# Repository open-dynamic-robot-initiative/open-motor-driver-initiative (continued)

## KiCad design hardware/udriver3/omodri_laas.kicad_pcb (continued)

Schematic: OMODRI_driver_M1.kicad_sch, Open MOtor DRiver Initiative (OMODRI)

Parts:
C74, C77: 1uF; C_0402_1005Metric; Rated Voltage 35V; Part No C1005X5R1V105K050BE; DigiKey 445-175218-1-ND
C75: 10uF; C_1210_3225Metric; Rated Voltage 75V; Part No C3225X7R1N106K250AC; Farnell 3416259
C76: 100nF; C_0603_1608Metric; Rated Voltage 100V; Part No GRM188R72A104KA35D; Farnell 1828921
C78: 1uF; C_0201_0603Metric; Rated Voltage 10V; Part No GRM033C81A105ME05D; DigiKey 490-13219-1-ND
C79: 47nF; C_0603_1608Metric; Rated Voltage 100V; Part No C1608X7S2A473K080AB; DigiKey 445-6032-1-ND
C80, C86, C87: 1.8nF; C_0201_0603Metric; Rated Voltage 50V; Part No GRM033R71E182KA12D; DigiKey 490-GRM033R71E182KA12DTR-ND
C81, C88, C89: 470nF; C_0201_0603Metric; Rated Voltage 25V; Part No GRM033R60J474ME90D; DigiKey 490-10410-1-ND
C82: 100nF; C_0201_0603Metric; Rated Voltage 10V; Part No GRM033R61E104KE14J; Farnell 3790414
C83, C84, C85: 1.8nF; C_0201_0603Metric; Rated Voltage 25V; Part No GRM033R71E182KA12D; DigiKey 490-GRM033R71E182KA12DTR-ND
D3: LED RED; LED_0402_1005Metric; Part No HSMC-C280; DigiKey 516-3060-1-ND
J11: Conn_01x03; AMASS_MR30PW-FB_1x03_P3.50mm_Horizontal
Q1, Q2, Q3: CSD88599Q5DC; VSON_CLIP_22; Part No CSD88599Q5DC; DigiKey 296-48289-1-ND
R7, R47: 10k; R_0201_0603Metric; Part No ERJ-1GNF1002C; DigiKey P122414CT-ND
R34, R38, R39: 100k; R_0402_1005Metric; Rated Voltage 50; Part No ERJ-2RKF1003X; DigiKey P100KLCT-ND
R35, R42, R44: 0.005; FC4L64; Part No FC4L64R005FER; DigiKey FC4L64R005FERCT-ND
R36, R43, R45: 5.1k; R_0402_1005Metric; Rated Voltage 50; Part No ERJ-2RKF5101X; DigiKey P5.10KLCT-ND
R37, R40, R41: 120; R_0201_0603Metric; Part No ERJ-1GNF1200C; DigiKey P122692CT-ND
R46: 470; R_0201_0603Metric; Part No ERJ-1GNF4701C; DigiKey P123031CT-ND
U19: DRV8353S; QFN-40-1EP_6x6mm_P0.5mm_EP4.6x4.6mm; Part No DRV8353SRTAT; DigiKey 296-DRV8353SRTATCT-ND

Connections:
/OMODRI_GPIO/DRV1_GPIO_EN: U19.31 (ENABLE); also elsewhere on the board
/OMODRI_GPIO/DRV_SPI_CLK: U19.29 (SCLK); also elsewhere on the board
/OMODRI_GPIO/DRV_SPI_SIMO: U19.28 (SDI); also elsewhere on the board
/OMODRI_GPIO/DRV_SPI_SOMI: R7.1, U19.27 (SDO); also elsewhere on the board
/OMODRI_GPIO/M1_Ia: C85.1, R41.1; also elsewhere on the board
/OMODRI_GPIO/M1_Ib: C84.1, R40.1; also elsewhere on the board
/OMODRI_GPIO/M1_Ic: C83.1, R37.1; also elsewhere on the board
/OMODRI_GPIO/M1_Va: C81.1, R34.2, R36.1; also elsewhere on the board
/OMODRI_GPIO/M1_Vb: C88.1, R38.2, R43.1; also elsewhere on the board
/OMODRI_GPIO/M1_Vc: C89.1, R39.2, R45.1; also elsewhere on the board
/OMODRI_GPIO/~DRV1_GPIO_CSn~: U19.30 (~SCS); also elsewhere on the board
/OMODRI_GPIO/~DRV1_GPIO_FAULTn~: R46.1, R47.1, U19.26 (~FAULT); also elsewhere on the board
/OMODRI_driver_M1/CPH: C79.1, U19.2 (CPH)
/OMODRI_driver_M1/CPL: C79.2, U19.1 (CPL)
/OMODRI_driver_M1/DVDD: C78.1, U19.38 (DVDD)
/OMODRI_driver_M1/GHA: Q1.1 (GH), U19.6 (GHA)
/OMODRI_driver_M1/GHB: Q2.1 (GH), U19.15 (GHB)
/OMODRI_driver_M1/GHC: Q3.1 (GH), U19.16 (GHC)
/OMODRI_driver_M1/GLA: Q1.22 (GL), U19.8 (GLA)
/OMODRI_driver_M1/GLB: Q2.22 (GL), U19.13 (GLB)
/OMODRI_driver_M1/GLC: Q3.22 (GL), U19.18 (GLC)
/OMODRI_driver_M1/INHA: U19.32 (INHA); also elsewhere on the board
/OMODRI_driver_M1/INHB: U19.34 (INHB); also elsewhere on the board
/OMODRI_driver_M1/INHC: U19.36 (INHC); also elsewhere on the board
/OMODRI_driver_M1/INLA: U19.33 (INLA); also elsewhere on the board
/OMODRI_driver_M1/INLB: U19.35 (INLB); also elsewhere on the board
/OMODRI_driver_M1/INLC: U19.37 (INLC); also elsewhere on the board
/OMODRI_driver_M1/MOTOR_CH1: J11.1, Q1.3 (VSW), Q1.4 (VSW), Q1.5 (VSW), Q1.6 (VSW), Q1.7 (VSW), Q1.8 (VSW), Q1.9 (VSW), Q1.10 (VSW), Q1.11 (VSW), R34.1
/OMODRI_driver_M1/MOTOR_CH2: J11.2, Q2.3 (VSW), Q2.4 (VSW), Q2.5 (VSW), Q2.6 (VSW), Q2.7 (VSW), Q2.8 (VSW), Q2.9 (VSW), Q2.10 (VSW), Q2.11 (VSW), R38.1
/OMODRI_driver_M1/MOTOR_CH3: J11.3, Q3.3 (VSW), Q3.4 (VSW), Q3.5 (VSW), Q3.6 (VSW), Q3.7 (VSW), Q3.8 (VSW), Q3.9 (VSW), Q3.10 (VSW), Q3.11 (VSW), R39.1
/OMODRI_driver_M1/OUT_M1_CH1: Q1.12 (PGND), Q1.13 (PGND), Q1.14 (PGND), Q1.15 (PGND), Q1.16 (PGND), Q1.17 (PGND), Q1.18 (PGND), Q1.19 (PGND), Q1.20 (PGND), R35.1
/OMODRI_driver_M1/OUT_M1_CH2: Q2.12 (PGND), Q2.13 (PGND), Q2.14 (PGND), Q2.15 (PGND), Q2.16 (PGND), Q2.17 (PGND), Q2.18 (PGND), Q2.19 (PGND), Q2.20 (PGND), R42.4
/OMODRI_driver_M1/OUT_M1_CH3: Q3.12 (PGND), Q3.13 (PGND), Q3.14 (PGND), Q3.15 (PGND), Q3.16 (PGND), Q3.17 (PGND), Q3.18 (PGND), Q3.19 (PGND), Q3.20 (PGND), R44.4
/OMODRI_driver_M1/SHA: Q1.2 (SH), U19.7 (SHA)
/OMODRI_driver_M1/SHB: Q2.2 (SH), U19.14 (SHB)
/OMODRI_driver_M1/SHC: Q3.2 (SH), U19.17 (SHC)
/OMODRI_driver_M1/SNA: C80.2, R35.3, U19.10 (SNA)
/OMODRI_driver_M1/SNB: C86.2, R42.2, U19.11 (SNB)
/OMODRI_driver_M1/SNC: C87.2, R44.2, U19.20 (SNC)
/OMODRI_driver_M1/SPA: C80.1, R35.2, U19.9 (SPA)
/OMODRI_driver_M1/SPB: C86.1, R42.3, U19.12 (SPB)
/OMODRI_driver_M1/SPC: C87.1, R44.3, U19.19 (SPC)
/OMODRI_driver_M1/VCP_DRV: C74.2, U19.5 (VCP)
/OMODRI_driver_M1/VGLS: C77.2, U19.40 (VGLS)
unnamed: D3.1 (K), R46.2
unnamed: R37.2, U19.21 (SOC)
unnamed: R40.2, U19.22 (SOB)
unnamed: R41.2, U19.23 (SOA)
REF_3V0_BUF: C82.1, U19.24 (VREF); also elsewhere on the board
VDD_3V3: D3.2 (A), R7.2, R47.2; also elsewhere on the board

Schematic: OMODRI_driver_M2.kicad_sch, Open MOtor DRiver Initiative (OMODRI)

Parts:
C90, C93: 1uF; C_0402_1005Metric; Rated Voltage 35V; Part No C1005X5R1V105K050BE; DigiKey 445-175218-1-ND
C91: 10uF; C_1210_3225Metric; Rated Voltage 75V; Part No C3225X7R1N106K250AC; Farnell 3416259
C92: 100nF; C_0603_1608Metric; Rated Voltage 100V; Part No GRM188R72A104KA35D; Farnell 1828921
C94: 1uF; C_0201_0603Metric; Rated Voltage 10V; Part No GRM033C81A105ME05D; DigiKey 490-13219-1-ND
C95: 47nF; C_0603_1608Metric; Rated Voltage 100V; Part No C1608X7S2A473K080AB; DigiKey 445-6032-1-ND
C96, C102, C103: 1.8nF; C_0201_0603Metric; Rated Voltage 50V; Part No GRM033R71E182KA12D; DigiKey 490-GRM033R71E182KA12DTR-ND
C97, C104, C105: 470nF; C_0201_0603Metric; Rated Voltage 25V; Part No GRM033R60J474ME90D; DigiKey 490-10410-1-ND
C98: 100nF; C_0201_0603Metric; Rated Voltage 10V; Part No GRM033R61E104KE14J; Farnell 3790414
C99, C100, C101: 1.8nF; C_0201_0603Metric; Rated Voltage 25V; Part No GRM033R71E182KA12D; DigiKey 490-GRM033R71E182KA12DTR-ND
D4: LED RED; LED_0402_1005Metric; Part No HSMC-C280; DigiKey 516-3060-1-ND
J12: Conn_01x03; AMASS_MR30PW-FB_1x03_P3.50mm_Horizontal
Q4, Q5, Q6: CSD88599Q5DC; VSON_CLIP_22; Part No CSD88599Q5DC; DigiKey 296-48289-1-ND
R48, R52, R53: 100k; R_0402_1005Metric; Rated Voltage 50; Part No ERJ-2RKF1003X; DigiKey P100KLCT-ND
R49, R56, R58: 0.005; FC4L64; Part No FC4L64R005FER; DigiKey FC4L64R005FERCT-ND
R50, R57, R59: 5.1k; R_0402_1005Metric; Rated Voltage 50; Part No ERJ-2RKF5101X; DigiKey P5.10KLCT-ND
R51, R54, R55: 120; R_0201_0603Metric; Part No ERJ-1GNF1200C; DigiKey P122692CT-ND
R60: 470; R_0201_0603Metric; Part No ERJ-1GNF4701C; DigiKey P123031CT-ND
R61: 10k; R_0201_0603Metric; Part No ERJ-1GNF1002C; DigiKey P122414CT-ND
U20: DRV8353S; QFN-40-1EP_6x6mm_P0.5mm_EP4.6x4.6mm; Part No DRV8353SRTAT; DigiKey 296-DRV8353SRTATCT-ND

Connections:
/OMODRI_GPIO/DRV2_GPIO_EN: U20.31 (ENABLE); also elsewhere on the board
/OMODRI_GPIO/DRV_SPI_CLK: U20.29 (SCLK); also elsewhere on the board
/OMODRI_GPIO/DRV_SPI_SIMO: U20.28 (SDI); also elsewhere on the board
/OMODRI_GPIO/DRV_SPI_SOMI: U20.27 (SDO); also elsewhere on the board
/OMODRI_GPIO/M2_Ia: C101.1, R55.1; also elsewhere on the board
/OMODRI_GPIO/M2_Ib: C100.1, R54.1; also elsewhere on the board
/OMODRI_GPIO/M2_Ic: C99.1, R51.1; also elsewhere on the board
/OMODRI_GPIO/M2_Va: C97.1, R48.2, R50.1; also elsewhere on the board
/OMODRI_GPIO/M2_Vb: C104.1, R52.2, R57.1; also elsewhere on the board
/OMODRI_GPIO/M2_Vc: C105.1, R53.2, R59.1; also elsewhere on the board
/OMODRI_GPIO/~DRV2_GPIO_CSn~: U20.30 (~SCS); also elsewhere on the board
/OMODRI_GPIO/~DRV2_GPIO_FAULTn~: R60.1, R61.1, U20.26 (~FAULT); also elsewhere on the board
/OMODRI_driver_M2/CPH: C95.1, U20.2 (CPH)
/OMODRI_driver_M2/CPL: C95.2, U20.1 (CPL)
/OMODRI_driver_M2/DVDD: C94.1, U20.38 (DVDD)
/OMODRI_driver_M2/GHA: Q4.1 (GH), U20.6 (GHA)
/OMODRI_driver_M2/GHB: Q5.1 (GH), U20.15 (GHB)
/OMODRI_driver_M2/GHC: Q6.1 (GH), U20.16 (GHC)
/OMODRI_driver_M2/GLA: Q4.22 (GL), U20.8 (GLA)
/OMODRI_driver_M2/GLB: Q5.22 (GL), U20.13 (GLB)
/OMODRI_driver_M2/GLC: Q6.22 (GL), U20.18 (GLC)
/OMODRI_driver_M2/INHA: U20.32 (INHA); also elsewhere on the board
/OMODRI_driver_M2/INHB: U20.34 (INHB); also elsewhere on the board
/OMODRI_driver_M2/INHC: U20.36 (INHC); also elsewhere on the board
/OMODRI_driver_M2/INLA: U20.33 (INLA); also elsewhere on the board
/OMODRI_driver_M2/INLB: U20.35 (INLB); also elsewhere on the board
/OMODRI_driver_M2/INLC: U20.37 (INLC); also elsewhere on the board
/OMODRI_driver_M2/MOTOR_CH1: J12.1, Q4.3 (VSW), Q4.4 (VSW), Q4.5 (VSW), Q4.6 (VSW), Q4.7 (VSW), Q4.8 (VSW), Q4.9 (VSW), Q4.10 (VSW), Q4.11 (VSW), R48.1
/OMODRI_driver_M2/MOTOR_CH2: J12.2, Q5.3 (VSW), Q5.4 (VSW), Q5.5 (VSW), Q5.6 (VSW), Q5.7 (VSW), Q5.8 (VSW), Q5.9 (VSW), Q5.10 (VSW), Q5.11 (VSW), R52.1
/OMODRI_driver_M2/MOTOR_CH3: J12.3, Q6.3 (VSW), Q6.4 (VSW), Q6.5 (VSW), Q6.6 (VSW), Q6.7 (VSW), Q6.8 (VSW), Q6.9 (VSW), Q6.10 (VSW), Q6.11 (VSW), R53.1
/OMODRI_driver_M2/OUT_M2_CH1: Q4.12 (PGND), Q4.13 (PGND), Q4.14 (PGND), Q4.15 (PGND), Q4.16 (PGND), Q4.17 (PGND), Q4.18 (PGND), Q4.19 (PGND), Q4.20 (PGND), R49.1
/OMODRI_driver_M2/OUT_M2_CH2: Q5.12 (PGND), Q5.13 (PGND), Q5.14 (PGND), Q5.15 (PGND), Q5.16 (PGND), Q5.17 (PGND), Q5.18 (PGND), Q5.19 (PGND), Q5.20 (PGND), R56.1
/OMODRI_driver_M2/OUT_M2_CH3: Q6.12 (PGND), Q6.13 (PGND), Q6.14 (PGND), Q6.15 (PGND), Q6.16 (PGND), Q6.17 (PGND), Q6.18 (PGND), Q6.19 (PGND), Q6.20 (PGND), R58.4
/OMODRI_driver_M2/SHA: Q4.2 (SH), U20.7 (SHA)
/OMODRI_driver_M2/SHB: Q5.2 (SH), U20.14 (SHB)
/OMODRI_driver_M2/SHC: Q6.2 (SH), U20.17 (SHC)
/OMODRI_driver_M2/SNA: C96.2, R49.3, U20.10 (SNA)
/OMODRI_driver_M2/SNB: C102.2, R56.3, U20.11 (SNB)
/OMODRI_driver_M2/SNC: C103.2, R58.2, U20.20 (SNC)
/OMODRI_driver_M2/SPA: C96.1, R49.2, U20.9 (SPA)
/OMODRI_driver_M2/SPB: C102.1, R56.2, U20.12 (SPB)
/OMODRI_driver_M2/SPC: C103.1, R58.3, U20.19 (SPC)
/OMODRI_driver_M2/VCP_DRV: C90.2, U20.5 (VCP)
/OMODRI_driver_M2/VGLS: C93.2, U20.40 (VGLS)
unnamed: D4.1 (K), R60.2
unnamed: R51.2, U20.21 (SOC)
unnamed: R54.2, U20.22 (SOB)
unnamed: R55.2, U20.23 (SOA)
REF_3V0_BUF: C98.1, U20.24 (VREF); also elsewhere on the board
VDD_3V3: D4.2 (A), R61.2; also elsewhere on the board

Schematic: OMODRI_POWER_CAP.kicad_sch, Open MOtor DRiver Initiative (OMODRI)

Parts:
C11, C114, C115, C116: 22uF; C_2220_5650Metric; Rated Voltage 100V; Part No C5750X7S2A226M280KB; DigiKey 445-C5750X7S2A226M280KBCT-ND
C112: 10nF; C_0201_0603Metric; Rated Voltage 25V; Part No GRM033R71E103KE14D; DigiKey 490-14454-1-ND
D11: TPD1E04U04; D_0201_0603Metric; Part No TPD1E04U04DPLT; DigiKey 296-47862-1-ND
J13: Conn_01x02; AMASS_XT30PW-M_1x02_P2.50mm_Horizontal
R62: 100k; R_0402_1005Metric; Rated Voltage 50; Part No ERJ-2RKF1003X; DigiKey P100KLCT-ND
R63: 5.1k; R_0402_1005Metric; Rated Voltage 50; Part No ERJ-2RKF5101X; DigiKey P5.10KLCT-ND

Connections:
/OMODRI_GPIO/M1_Vbus: C112.1, D11.1 (IO), R62.2, R63.1; also elsewhere on the board

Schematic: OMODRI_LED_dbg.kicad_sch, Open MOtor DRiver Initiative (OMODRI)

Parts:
D5: WS2812B; LED_WS2812B_PLCC4_5.0x5.0mm_P3.2mm; Part No WS2812B 5050; DigiKey 1568-COM-16347CT-ND

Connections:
/OMODRI_GPIO/WS2812B_CMD: D5.4 (DIN); also elsewhere on the board
VDD_3V3: D5.1 (VDD); also elsewhere on the board

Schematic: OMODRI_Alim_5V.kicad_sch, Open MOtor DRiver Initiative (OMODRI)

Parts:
C9: 10uF; C_1210_3225Metric; Rated Voltage 75V; Part No C3225X7R1N106K250AC; Farnell 3416259
C10, C30: 100nF; C_0603_1608Metric; Rated Voltage 100V; Part No GRM188R72A104KA35D; Farnell 1828921
C12: 1uF; C_0201_0603Metric; Rated Voltage 10V; Part No GRM033C81A105ME05D; DigiKey 490-13219-1-ND
C13: 10uF; C_0603_1608Metric; Rated Voltage 10V; Part No GRM188R61A106ME69D; DigiKey 490-10475-1-ND
L1: 22uH; L_Wuerth_MAPI-4020; Part No MPL-SE4030-220
R3, R69: 100k; R_0201_0603Metric; Part No ERJ-1GNF1003C; DigiKey P122655CT-ND
R68, R70, R71, R72: 76.8k; R_0201_0603Metric
U2: MP4572GQB

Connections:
unnamed: R70.1, R71.2, R72.1

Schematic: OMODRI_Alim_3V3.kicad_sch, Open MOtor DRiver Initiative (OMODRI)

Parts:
C14, C16, C19: 10uF; C_0603_1608Metric; Rated Voltage 10V; Part No GRM188R61A106ME69D; DigiKey 490-10475-1-ND
C15, C17: 1uF; C_0201_0603Metric; Rated Voltage 10V; Part No GRM033C81A105ME05D; DigiKey 490-13219-1-ND
FB1, FB2: 220R@100MHz; L_0603_1608Metric; Part No BLM18SG221TN1D; DigiKey 490-5225-1-ND
R5: 100k; R_0201_0603Metric; Part No ERJ-1GNF1003C; DigiKey P122655CT-ND
R6: 22.1k; R_0201_0603Metric; Part No ERJ-1GNF2212C; DigiKey P122837CT-ND
U3: MPM3804GG; QFN-10_2x2mm_P0.5mm; Part No MPM3804GG; DigiKey 1589-1982-1-ND

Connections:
/Power distribution/OMODRI_Alim_3V3/3V3: C19.1, FB1.2, FB2.2, R5.1, U3.6 (VOUT), U3.7 (VOUT), U3.8 (VOUT)
/Power distribution/OMODRI_Alim_3V3/FB_3V3: R5.2, R6.1, U3.9 (FB)
/Power distribution/OMODRI_Alim_3V3/SW: U3.2 (SW), U3.3 (SW), U3.4 (SW)
VDDA_3V3: C16.1, C17.1, FB2.1; also elsewhere on the board
VDD_3V3: C14.1, C15.1, FB1.1; also elsewhere on the board

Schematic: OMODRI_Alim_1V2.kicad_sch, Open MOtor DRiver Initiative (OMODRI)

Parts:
C21, C22: 10uF; C_0603_1608Metric; Rated Voltage 10V; Part No GRM188R61A106ME69D; DigiKey 490-10475-1-ND
C23: 1uF; C_0201_0603Metric; Rated Voltage 10V; Part No GRM033C81A105ME05D; DigiKey 490-13219-1-ND
FB3: 220R@100MHz; L_0603_1608Metric; Part No BLM18SG221TN1D; DigiKey 490-5225-1-ND
R8, R9: 100k; R_0201_0603Metric; Part No ERJ-1GNF1003C; DigiKey P122655CT-ND
U4: MPM3804GG; QFN-10_2x2mm_P0.5mm; Part No MPM3804GG; DigiKey 1589-1982-1-ND

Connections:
/Power distribution/OMODRI_Alim_1V2/1V2: C21.1, FB3.2, R8.1, U4.6 (VOUT), U4.7 (VOUT), U4.8 (VOUT)
/Power distribution/OMODRI_Alim_1V2/FB_1V2: R8.2, R9.1, U4.9 (FB)
/Power distribution/OMODRI_Alim_1V2/SW: U4.2 (SW), U4.3 (SW), U4.4 (SW)
VDD_1V2: C22.1, C23.1, FB3.1; also elsewhere on the board

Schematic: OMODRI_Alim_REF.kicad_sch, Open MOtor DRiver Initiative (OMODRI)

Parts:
C26: 100nF; C_0201_0603Metric; Rated Voltage 10V; Part No GRM033R61E104KE14J; DigiKey 490-14571-1-ND
C27, C29: 1uF; C_0201_0603Metric; Rated Voltage 10V; Part No GRM033C81A105ME05D; DigiKey 490-13219-1-ND
C28: 10uF; C_0603_1608Metric; Rated Voltage 10V; Part No GRM188R61A106ME69D; DigiKey 490-10475-1-ND
U5: LT6654AIS6-3; TSOT-23-6; Part No LT6654AIS6-3#TRMPBF; DigiKey LT6654AIS6-3#TRMPBFCT-ND

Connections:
REF_3V0_BUF: C28.1, C29.1, U5.6 (VOUT); also elsewhere on the board
VDDA_3V3: C26.1, C27.1, U5.4 (VIN); also elsewhere on the board

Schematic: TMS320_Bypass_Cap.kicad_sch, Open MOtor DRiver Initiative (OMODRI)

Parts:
C34, C35, C36, C37, C38, C39, C40, C41, C42, C43, C44, C45, C46, C47, C48, C49, C50, C51, C52, C53, C54, C55, C56: 100nF; C_0201_0603Metric; Rated Voltage 10V; Part No GRM033R61E104KE14J; Farnell 3790414
R10, R13: 120; R_0201_0603Metric; Part No ERJ-1GNF1200C; DigiKey P122692CT-ND

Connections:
VDD_1V2: C34.1, C35.1, C36.1, C37.1, C38.1, C39.1, C40.1, R10.1, R13.1; also elsewhere on the board
VDD_3V3: C41.1, C42.1, C43.1, C44.1, C45.1, C46.1, C47.1, C48.1, C49.1, C50.1, C51.1, C52.1, C53.1, C54.1, C55.1, C56.1; also elsewhere on the board

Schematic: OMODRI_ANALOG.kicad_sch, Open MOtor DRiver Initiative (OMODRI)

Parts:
D2, D6, D7, D8, D9, D10, D12, D13: TPD1E04U04; D_0201_0603Metric; Part No TPD1E04U04DPLT; DigiKey 296-47862-1-ND
U1: TMS320F28388D; NFBGA_337; Part No F28388DZWTS; DigiKey 296-F28388DZWTS-ND

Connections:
/OMODRI_GPIO/ANALOG_IN1: D12.1 (IO), U1.T4 (ADCIN14); also elsewhere on the board
/OMODRI_GPIO/ANALOG_IN2: D13.1 (IO), U1.U4 (ADCIN15); also elsewhere on the board
/OMODRI_GPIO/M1_Ia: U1.U1 (ADCINA0); also elsewhere on the board
/OMODRI_GPIO/M1_Ib: U1.V2 (ADCINB0); also elsewhere on the board
/OMODRI_GPIO/M1_Ic: U1.T5 (ADCIND0); also elsewhere on the board
/OMODRI_GPIO/M1_Va: D9.1 (IO), U1.U2 (ADCINA2); also elsewhere on the board
/OMODRI_GPIO/M1_Vb: D10.1 (IO), U1.V3 (ADCINB2); also elsewhere on the board
/OMODRI_GPIO/M1_Vbus: U1.R3 (ADCINC2); also elsewhere on the board
/OMODRI_GPIO/M1_Vc: D8.1 (IO), U1.T6 (ADCIND2); also elsewhere on the board
/OMODRI_GPIO/M2_Ia: U1.T1 (ADCINA1); also elsewhere on the board
/OMODRI_GPIO/M2_Ib: U1.W2 (ADCINB1); also elsewhere on the board
/OMODRI_GPIO/M2_Ic: U1.U5 (ADCIND1); also elsewhere on the board
/OMODRI_GPIO/M2_Va: D6.1 (IO), U1.T2 (ADCINA3); also elsewhere on the board
/OMODRI_GPIO/M2_Vb: D7.1 (IO), U1.W3 (ADCINB3); also elsewhere on the board
/OMODRI_GPIO/M2_Vc: D2.1 (IO), U1.U6 (ADCIND3); also elsewhere on the board
REF_3V0_BUF: U1.R1 (VREFHIC), U1.V1 (VREFHIA), U1.V5 (VREFHID), U1.W5 (VREFHIB); also elsewhere on the board

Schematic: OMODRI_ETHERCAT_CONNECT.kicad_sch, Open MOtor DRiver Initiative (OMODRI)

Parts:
J15, J16: ADM6_ADF6; ADF6-10-XX.X-XXX-4-X-A-XR; Part No ADF6-10-03.5-L-4-2-A; DigiKey 612-ADF6-10-03.5-L-4-2-A-TR-ND

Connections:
/JTAG + CLOCK + RESET/25MHz_OSC_SRC: J16.C03; also elsewhere on the board
/OMODRI_GPIO/ANALOG_IN2: J16.A08; also elsewhere on the board
/OMODRI_GPIO/ECAT0_INT: J15.A06; also elsewhere on the board
/OMODRI_GPIO/ECAT1_INT: J16.A06; also elsewhere on the board
/OMODRI_GPIO/ESC_I2C_SCL: J15.C01; also elsewhere on the board
/OMODRI_GPIO/ESC_I2C_SDA: J15.D01; also elsewhere on the board
/OMODRI_GPIO/ESC_LED_ERR: J15.B01; also elsewhere on the board
/OMODRI_GPIO/ESC_LED_LINK0_ACTIVE: J15.B02; also elsewhere on the board
/OMODRI_GPIO/ESC_LED_LINK1_ACTIVE: J15.A02; also elsewhere on the board
/OMODRI_GPIO/ESC_LED_RUN: J15.A01; also elsewhere on the board
/OMODRI_GPIO/ESC_MDIO_CLK: J15.D03; also elsewhere on the board
/OMODRI_GPIO/ESC_MDIO_DATA: J15.B04; also elsewhere on the board
/OMODRI_GPIO/ESC_PHY0_LINKSTATUS: J15.C03; also elsewhere on the board
/OMODRI_GPIO/ESC_PHY1_LINKSTATUS: J16.A02; also elsewhere on the board
/OMODRI_GPIO/ESC_RX0_CLK: J15.C09; also elsewhere on the board
/OMODRI_GPIO/ESC_RX0_D0: J15.D10; also elsewhere on the board
/OMODRI_GPIO/ESC_RX0_D1: J15.B10; also elsewhere on the board
/OMODRI_GPIO/ESC_RX0_D2: J15.C10; also elsewhere on the board
/OMODRI_GPIO/ESC_RX0_D3: J15.A10; also elsewhere on the board
/OMODRI_GPIO/ESC_RX0_DV: J15.D07; also elsewhere on the board
/OMODRI_GPIO/ESC_RX0_ERR: J15.D09; also elsewhere on the board
/OMODRI_GPIO/ESC_RX1_CLK: J16.B02; also elsewhere on the board
/OMODRI_GPIO/ESC_RX1_D0: J16.C05; also elsewhere on the board
/OMODRI_GPIO/ESC_RX1_D1: J16.B06; also elsewhere on the board
/OMODRI_GPIO/ESC_RX1_D2: J16.D07; also elsewhere on the board
/OMODRI_GPIO/ESC_RX1_D3: J16.C07; also elsewhere on the board
/OMODRI_GPIO/ESC_RX1_DV: J16.D03; also elsewhere on the board
/OMODRI_GPIO/ESC_RX1_ERR: J16.A01; also elsewhere on the board
/OMODRI_GPIO/ESC_TX0_CLK: J15.D05; also elsewhere on the board
/OMODRI_GPIO/ESC_TX0_D0: J15.B06; also elsewhere on the board
/OMODRI_GPIO/ESC_TX0_D1: J15.A08; also elsewhere on the board
/OMODRI_GPIO/ESC_TX0_D2: J15.C07; also elsewhere on the board
/OMODRI_GPIO/ESC_TX0_D3: J15.B08; also elsewhere on the board
/OMODRI_GPIO/ESC_TX0_ENA: J15.C05; also elsewhere on the board
/OMODRI_GPIO/ESC_TX1_CLK: J16.A04; also elsewhere on the board
/OMODRI_GPIO/ESC_TX1_D0: J16.B04; also elsewhere on the board
/OMODRI_GPIO/ESC_TX1_D1: J16.D01; also elsewhere on the board
/OMODRI_GPIO/ESC_TX1_D2: J16.C01; also elsewhere on the board
/OMODRI_GPIO/ESC_TX1_D3: J16.B01; also elsewhere on the board
/OMODRI_GPIO/ESC_TX1_ENA: J16.D05; also elsewhere on the board
/OMODRI_GPIO/GPIO125_SPI_CS2_n: J16.B08; also elsewhere on the board
/OMODRI_GPIO/SPI_CLK: J16.B10; also elsewhere on the board
/OMODRI_GPIO/SPI_SIMO: J16.A10; also elsewhere on the board
/OMODRI_GPIO/SPI_SOMI: J16.D09; also elsewhere on the board
/OMODRI_GPIO/~ESC_PHY_RESETn~: J15.A04; also elsewhere on the board
/OMODRI_GPIO/~SPI_CSn~_BOOT_MODE1: J16.C09; also elsewhere on the board
VDD_3V3: J15.C02, J15.C04, J15.C06, J15.C08, J15.D02, J15.D04, J15.D06, J15.D08, J16.A03, J16.A05, J16.A07, J16.A09, J16.B03, J16.B05, J16.B07, J16.B09; also elsewhere on the board

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
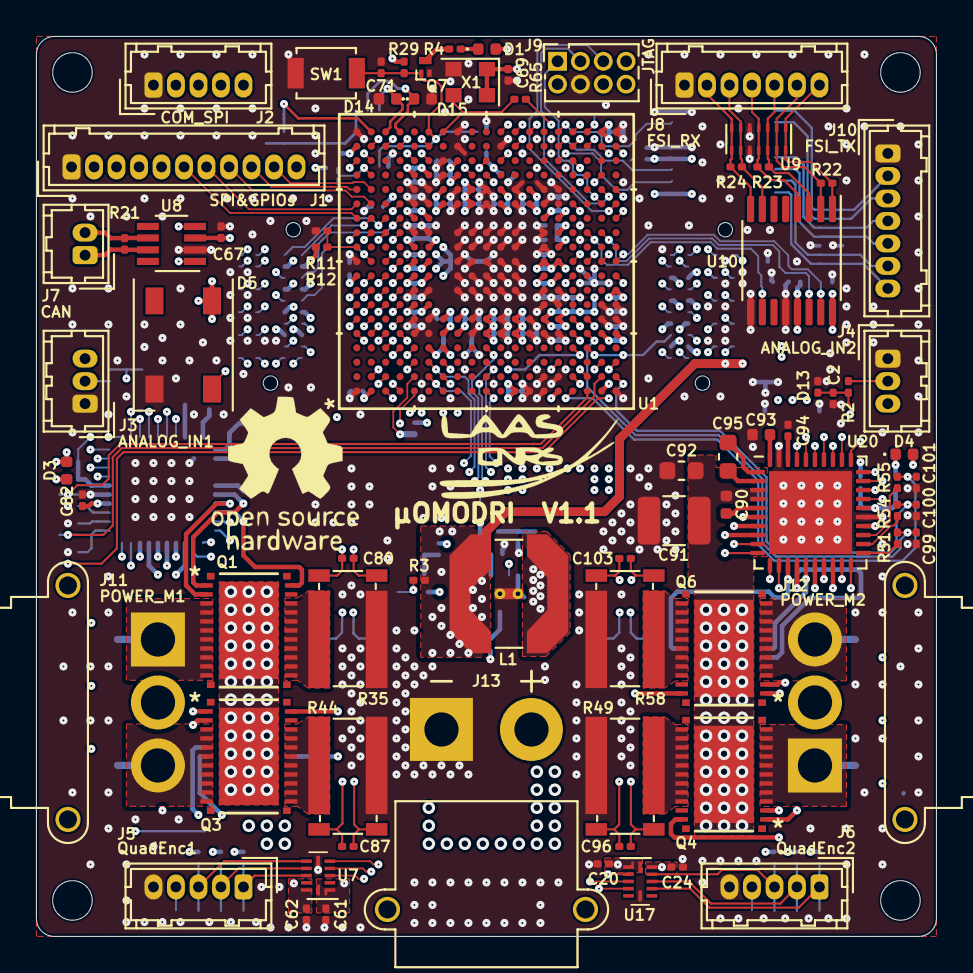
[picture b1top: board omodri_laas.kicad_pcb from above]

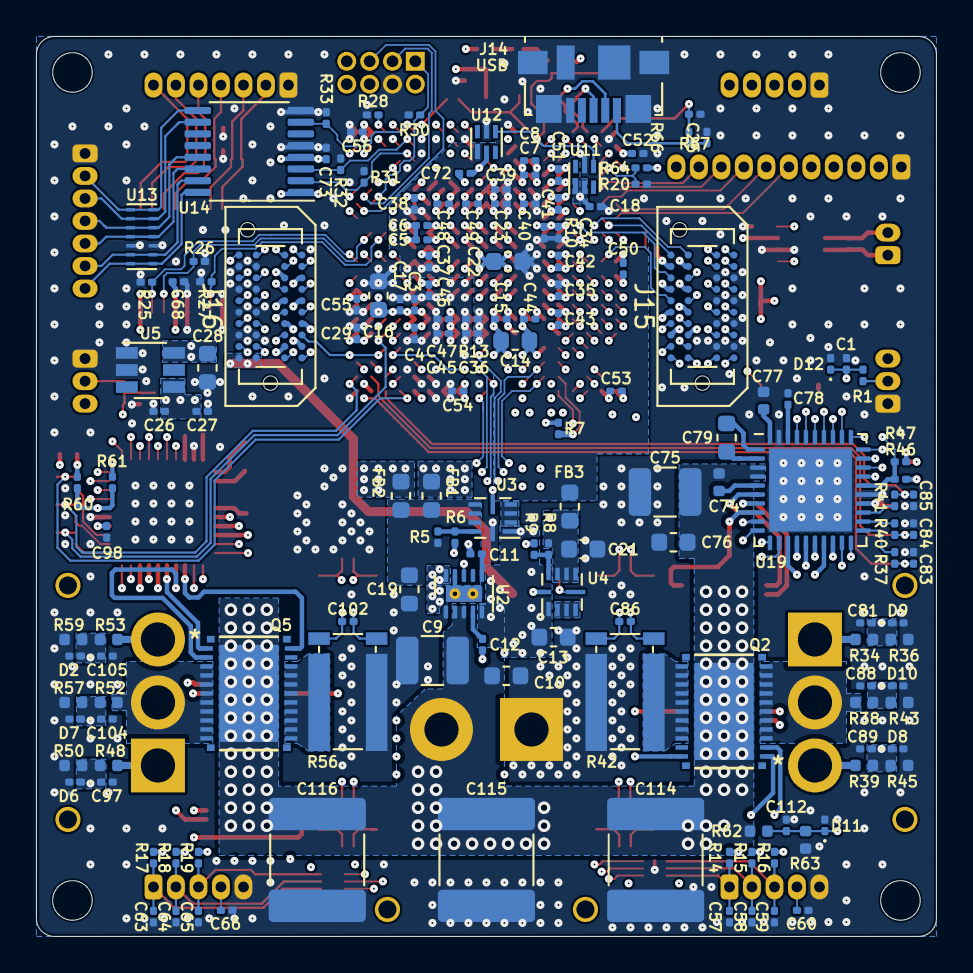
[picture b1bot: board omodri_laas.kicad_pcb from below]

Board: 6 copper layers, 50.0 x 50.0 mm, 237 parts (156 on the bottom side), 219 nets.

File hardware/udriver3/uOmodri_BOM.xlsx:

Reference | Value |  | Part No | DigiKey | Mouser | Farnell | RS | Qty/PCB
C1, C2, C11, C71, C81, C83, C84, C85, C88, C89, C97, C99, C100, C101, C104, C10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 | 10nF | Capacitor_SMD:C_0201_0603Metric | GRM033R71E103KE14D | 490-14454-1-ND | 81-GRM033R71E103KE4D | 2990696 | 185-2059 | 17
C3, C4, C5, C6, C7, C8, C18, C20, C24, C25, C26, C34, C35, C36, C37, C38, C39, 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 | 100nF | Capacitor_SMD:C_0201_0603Metric | GRM033C71A104KE14D | 490-14450-1-ND | 81-GRM033C71A104KE4D | 2990681 | 185-1751 | 43
C9, C75, C91 | 10uF | Capacitor_SMD:C_1210_3225Metric | C3225X7R1N106K250AC | 445-C3225X7R1N106K250ACCT-ND | 810-C3225X7R1N106K25 | 3416259 | xxx | 3
C10, C76, C92 | 100nF | Capacitor_SMD:C_0603_1608Metric | GRM188R72A104KA35D | 490-3285-1-ND | 81-GRM188R72A104KA35 | 1828921 | xxx | 3
C12, C15, C17, C23, C27, C29, C60, C66, C78, C94 | 1uF | Capacitor_SMD:C_0201_0603Metric | GRM033C81A105ME05D | 490-13219-1-ND | 81-GRM033C81A105ME5D | 3238032 | xxx | 10
C13, C14, C16, C19, C21, C22, C28 | 10uF | Capacitor_SMD:C_0603_1608Metric | GRM188R61A106ME69D | 490-10475-1-ND | 81-GRM188R61A106ME9D | 2456110 | 113-8702 | 7
C74, C77, C90, C93 | 1uF | Capacitor_SMD:C_0402_1005Metric | C1005X5R1V105K050BE | 445-175218-1-ND | 810-C1005X5R1V105KE | 3416060 | xxx | 4
C79, C95 | 47nF | Capacitor_SMD:C_0603_1608Metric | C1608X7S2A473K080AB | 445-6032-1-ND | 810-C1608X7S2A473K | 2906791 | xxx | 2
C57, C58, C59, C63, C64, C65, C80, C86, C87, C96, C102, C103 | 1nF | Capacitor_SMD:C_0201_0603Metric | GRM033R71H102KA12D | 490-10682-1-ND | 81-GRM033R71H102KA2D | 2990701 | 185-2113 | 12
C114, C115, C116 | 22uF | Capacitor_SMD:C_2220_5650Metric | C5750X7S2A226M280KB | 445-C5750X7S2A226M280KBCT-ND | 810-C5750X7S2A226280 | 3416277 | xxx | 3
D1 | LED GREEN | LED_SMD:LED_0402_1005Metric | HSMG-C280 | 516-3066-1-ND | 630-HSMG-C280 | 2494322 | 867-6560 | 1
D3, D4 | LED RED | LED_SMD:LED_0402_1005Metric | HSMC-C280 | 516-3060-1-ND | 630-HSMC-C280 | 2494321 | xxx | 2
D5 | WS2812B | LED_SMD:LED_WS2812B_PLCC4_5.0x5.0mm_P3.2mm | WS2812B | 1568-COM-16347CT-ND | 474-COM-16346 | xxx | xxx | 1
D2, D6, D7, D8, D9, D10, D11, D12, D13 | TPD1E04U04 | udriver3:D_0201_0603Metric | TPD1E04U04DPLT | 296-47862-1-ND | 595-TPD1E04U04DPLT | xxx | xxx | 9
D14, D15 | ESD321 | udriver3:D_0402_1005Metric | ESD321DPYR | 296-51108-1-ND | 595-ESD321DPYR | xxx | xxx | 2
FB1, FB2, FB3 | 220R@100MHz | Inductor_SMD:L_0603_1608Metric | BLM18SG221TN1D | 490-5225-1-ND | 81-BLM18SG221TN1D | 1515753 | 792-6271 | 3
J1 | Conn_01x11 | udriver3:Hirose_DF13-11P-1.25DSA_1x11_P1.25mm_Vertical | DF13-11P-1.25DSA | DF13-11P-1.25DSA-ND | 798-DF13-11P-1.25DSA | xxx | xxx | 1
J2, J5, J6 | Conn_01x05 | udriver3:Hirose_DF13-05P-1.25DSA_1x05_P1.25mm_Vertical | DF13-5P-1.25DSA | H2194-ND | 798-DF13-5P-1.25DSA | 2427589 | 503-7912 | 3
J3, J4 | Conn_01x03 | udriver3:Hirose_DF13-03P-1.25DSA_1x03_P1.25mm_Vertical | DF13-3P-1.25DSA | H2192-ND | 798-DF13-3P-1.25DSA | 2916340 | 175-0666 | 2
J7 | Conn_01x02 | udriver3:Hirose_DF13-02P-1.25DSA_1x02_P1.25mm_Vertical | DF13-2P-1.25DSA | H2191-ND | 798-DF13-2P-1.25DSA | 2427585 | xxx | 1
J9 | Conn_02x04_Odd_Even | udriver3:PinSocket_2x04_P1.27mm_Vertical | 20021311-00008T4LF | 609-3753-ND | 649-221311-00008T4LF | 2892503 | xxx | 1
J8, J10 | Conn_01x07 | udriver3:Hirose_DF13-07P-1.25DSA_1x07_P1.25mm_Vertical | DF13-7P-1.25DSA | H2196-ND | 798-DF13-7P-1.25DSA | xxx | xxx | 2
J11, J12 | Conn_01x03 | udriver3:AMASS_MR30PW-FB_1x03_P3.50mm_Horizontal |  |  |  |  |  | 2
J13 | Conn_01x02 | udriver3:AMASS_XT30PW-M_1x02_P2.50mm_Horizontal |  |  |  |  |  | 1
J14 | USB_B_Micro | udriver3:USB_Micro-B_Molex_47346-0001 | 473460001 | WM17141CT-ND | 538-47346-0001 | 1568026 | 702-5475 | 1
J15, J16 | ADM6_ADF6 | udriver3:ADF6-10-XX.X-XXX-4-X-A-XR | ADF6-10-03.5-L-4-2-A | 612-ADF6-10-03.5-L-4-2-A-TR-ND | 200-ADF6-10-3.5-L42A | 3462763 | 202-7885 | 2
L1 | 22uH | udriver3:L_coilcraft_LPS62xx | LPS6235-223MR | XC3163CT-ND | 994-LPS6235-223MRC | 2408291 | xxx | 1
Q1, Q2, Q3, Q4, Q5, Q6 | CSD88599Q5DC | udriver3:VSON_CLIP_22 | CSD88599Q5DC | 296-48289-1-ND | 595-CSD88599Q5DC | 2766880 | xxx | 6
Q7 | NX7002BKM | Package_DFN_QFN:Diodes_DFN1006-3 | NX7002BKMYL | 1727-2232-1-ND | 771-NX7002BKMYL | 2498574 | xxx | 1
R1, R2, R7, R10, R13, R21, R37, R40, R41, R51, R54, R55 | 120 | Resistor_SMD:R_0201_0603Metric | ERJ-1GNF1200C | P122692CT-ND | 667-ERJ-1GNF1200C | 2396857 | xxx | 12
R3, R5, R8, R9 | 100k | Resistor_SMD:R_0201_0603Metric | ERJ-1GNF1003C | P122655CT-ND | 667-ERJ-1GNF1003C | 2302389 | 179-7130 | 4
R6 | 22.1k | Resistor_SMD:R_0201_0603Metric | ERJ-1GNF2212C | P122837CT-ND | 667-ERJ-1GNF2212C | 3335196 | xxx | 1
R14, R15, R16, R17, R18, R19, R30 | 1k | Resistor_SMD:R_0201_0603Metric | ERJ-1GNF1001C | P122413CT-ND | 667-ERJ-1GNF1001C | 2302336 | 179-7127 | 7
R22, R23, R24 | 100 | Resistor_SMD:R_0201_0603Metric | ERJ-1GNF1000C | P122654CT-ND | 667-ERJ-1GNF1000C | 2302309 | 179-7123 | 3
R25, R26, R27, R28, R29, R31, R32, R33, R47, R61 | 10k | Resistor_SMD:R_0201_0603Metric | ERJ-1GNF1002C | P122414CT-ND | 667-ERJ-1GNF1002C | 2302362 | 176-3597 | 10
R34, R38, R39, R48, R52, R53, R62 | 100k | Resistor_SMD:R_0402_1005Metric | ERJ-2RKF1003X | P100KLCT-ND | 667-ERJ-2RKF1003X | 2302839 | 732-5255 | 7
R35, R42, R44, R49, R56, R58 | 5.0000000000000001E-3 | udriver3:FC4L64 | FC4L64R005FER | FC4L64R005FERCT-ND | 588-FC4L64R005FER | 2363991 | 126-0365 | 6
R36, R43, R45, R50, R57, R59, R63 | 5.1k | Resistor_SMD:R_0402_1005Metric | ERJ-2RKF5101X | P5.10KLCT-ND | 667-ERJ-2RKF5101X | 2302709 | 732-5536 | 7
R4, R46, R60 | 470 | Resistor_SMD:R_0201_0603Metric | ERJ-1GNF4701C | P123031CT-ND | 667-ERJ-1GNF4701C | 2302353 | 179-7160 | 3
SW1 | B3U-3100P | Button_Switch_SMD:SW_SPST_B3U-1000P | B3U-1000P | SW1020CT-ND | 653-B3U-1000P | 1333652 | 419-867 | 1
U1 | F28388DZWTS | udriver3:NFBGA_337 | TMS320F28388D | 296-F28388DZWTS-ND | 595-F28388DZWTS | xxx | xxx | 1
U2 | MAX17502FxTB | udriver3:TDFN-10-1EP_2x3mm_P0.5mm_EP0.9x2mm_ThermalVias | MAX17502FATB+T | MAX17502FATB+TCT-ND | 700-MAX17502FATB+T | 2514327 | 190-8188 | 1
U3, U4 | MPM3804GG | udriver3:QFN-10_2x2mm_P0.5mm | MPM3804GG | 1589-1982-1-ND | 946-MPM3804GG-Z | 3358188 | xxx | 2
U5 | LT6654AIS6-3 | Package_TO_SOT_SMD:TSOT-23-6 | LT6654AIS6-3#TRMPBF | LT6654AIS6-3#TRMPBFCT-ND | 584-6654AIS63TRMPBF | 2761957 | xxx | 1
U7, U17 | LSF0204RUT | Package_DFN_QFN:Texas_R_PUQFN-N12 | LSF0204RUTR | 296-40404-1-ND | 595-LSF0204RUTR | xxx | xxx | 2
U8 | TCAN332G | Package_TO_SOT_SMD:TSOT-23-8 | TCAN332GDCNR | 296-48677-1-ND | 595-TCAN332GDCNR | 3009409 | xxx | 1
U10 | DSLVDS1048 | Package_SO:TSSOP-16_4.4x5mm_P0.65mm | DSLVDS1048PWR | 296-51106-1-ND | 595-DSLVDS1048PWR | xxx | xxx | 1
U11 | TPS3703-3.3 | Package_SON:WSON-6_1.5x1.5mm_P0.5mm | TPS3703A7330DSERQ1 | 296-TPS3703A7330DSERQ1CT-ND | 595-S3703A7330DSERQ1 | xxx | xxx | 1
U12 | TPS3703-1.2 | Package_SON:WSON-6_1.5x1.5mm_P0.5mm | TPS3703A7120DSERQ1 | 296-TPS3703A7120DSERQ1CT-ND | 595-S3703A7120DSERQ1 | xxx | xxx | 1
U9, U13 | TPD6E05U06 | udriver3:USON_14 | TPD6E05U06RVZR | 296-39349-1-ND | 595-TPD6E05U06RVZR | xxx | xxx | 2
U14 | DSLVDS1047 | Package_SO:TSSOP-16_4.4x5mm_P0.65mm | DSLVDS1047PWR | 296-50740-1-ND | 595-DSLVDS1047PWR | xxx | xxx | 1
U19, U20 | DRV8353S | Package_DFN_QFN:QFN-40-1EP_6x6mm_P0.5mm_EP4.6x4.6mm | DRV8353SRTAT | 296-DRV8353SRTATCT-ND | 595-DRV8353SRTAT | xxx | xxx | 2
X1 | ASTX-H12-25.000MHZ-T | udriver3:TCXO_SMD_Abracon_ASTX-H12-4Pin_2.5x2.0mm | ASTX-H12-25.000MHZ-T | 535-12041-1-ND | 815-ASTX-H12-25T | xxx | xxx | 1

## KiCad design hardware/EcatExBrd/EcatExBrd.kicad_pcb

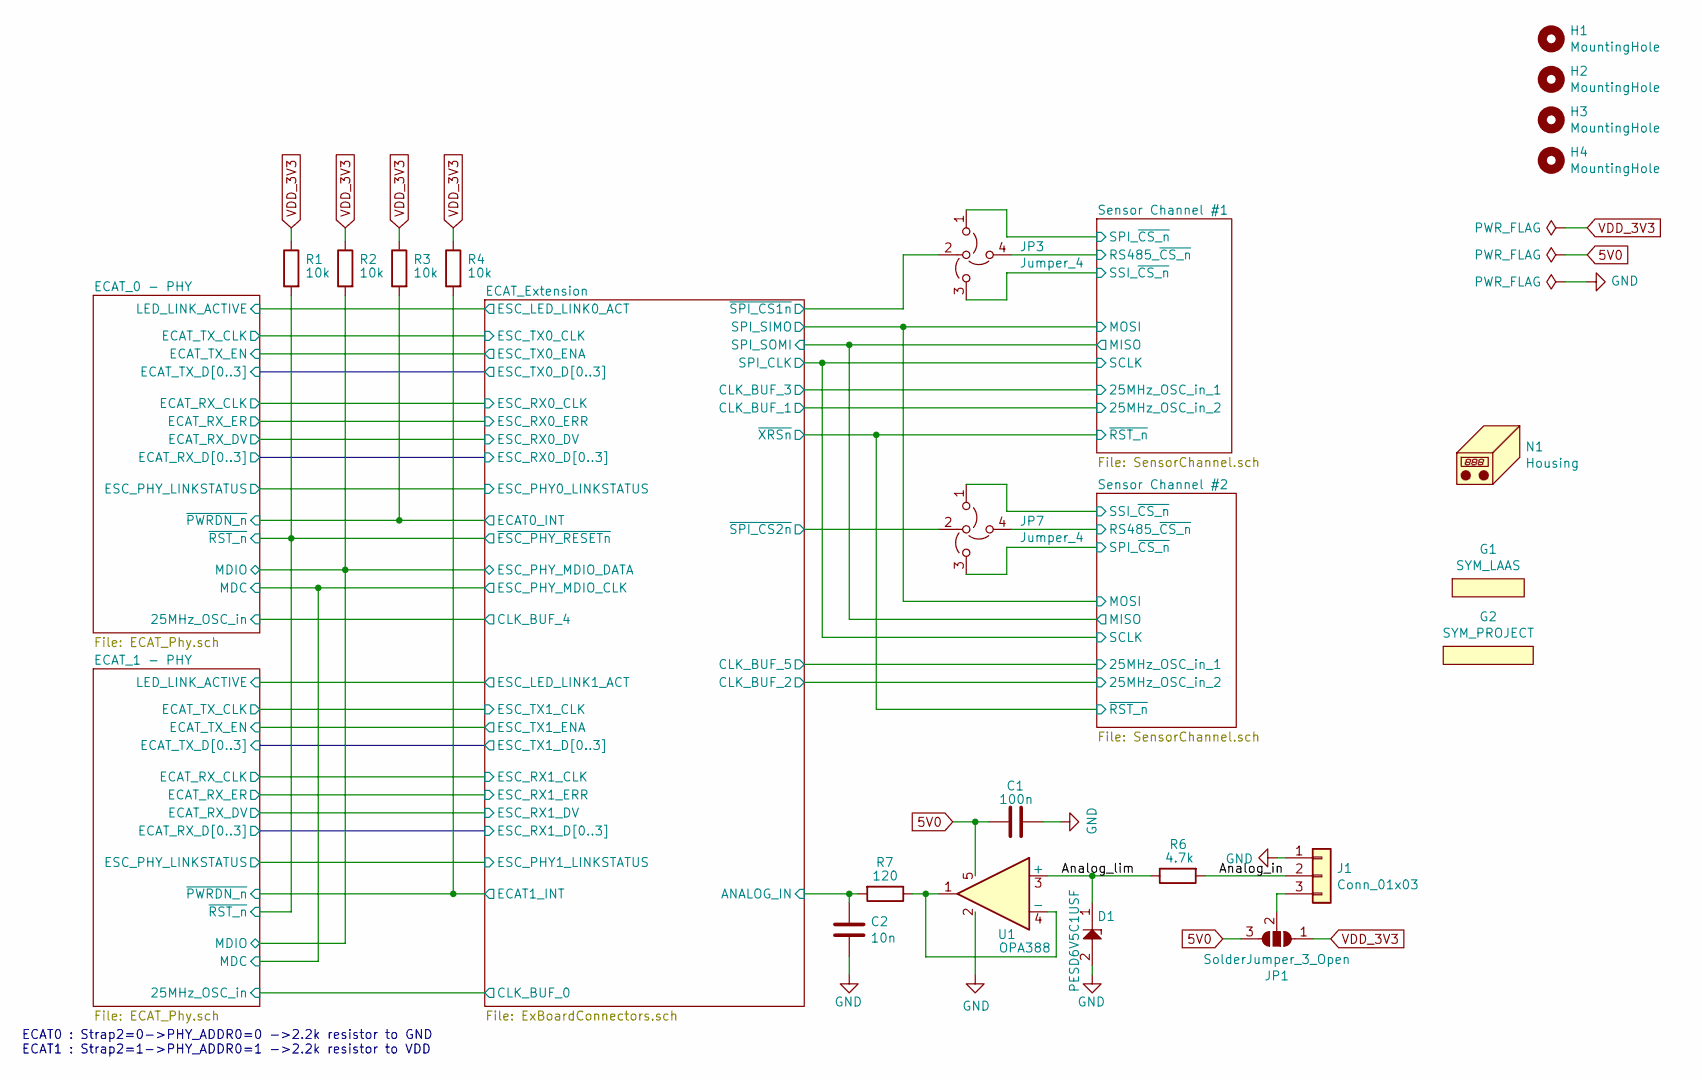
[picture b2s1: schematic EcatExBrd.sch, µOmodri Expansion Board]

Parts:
C1: 100n; C_0201_0603Metric; Part No GRM033R61C104KE84D; DigiKey 490-9985-1-ND
C2: 10n; C_0201_0603Metric; Part No GRM033R71E103KE14D; DigiKey 490-14454-1-ND
D1: PESD6V5C1USF; Diodes_DSN0603-2_0.6x0.3mm_P0.4mm; Part No PESD6V5C1USFYL; DigiKey PESD6V5C1USFYL-ND
G1: SYM_LAAS; logo_laas
G2: SYM_PROJECT; logo_OpenHardware
H1, H2, H3, H4: MountingHole; MountingHole_2.2mm_M2
J1: Conn_01x03; Hirose_DF13-03P-1.25DSA_1x03_P1.25mm_Vertical; Part No DF13-3P-1.25DSA; DigiKey H2192-ND
JP1: SolderJumper_3_Open; SolderJumper-3_0201_0603Metric_Open_Pad; Part No ERJ-1GN0R00C; DigiKey P15979CT-ND
JP3, JP7: Jumper_4; Harwin_M50_04_P1.27mm_cross_Vertical
N1: Housing; uOmodri_laas
R1, R2, R3, R4: 10k; R_0201_0603Metric; Part No ERJ-1GNF1002C; DigiKey P122414CT-ND
R6: 4.7k; R_0201_0603Metric; Part No ERJ-1GNF4701C; DigiKey P123031CT-ND
R7: 120; R_0201_0603Metric; Part No ERJ-1GNF1200C; DigiKey P122692CT-ND
U1: OPA388; SOT-23-5; Part No OPA388IDBV; DigiKey 296-53471-1-ND

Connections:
5V0: C1.1, JP1.3 (B), U1.5; also elsewhere on the board
/Analog_in: J1.2, R6.2
/Analog_lim: D1.1, R6.1, U1.3 (+)
/ECAT_Extension/ANALOG_IN: C2.1, R7.2; also elsewhere on the board
/ECAT_Extension/ECAT0_INT: R3.2; also elsewhere on the board
/ECAT_Extension/ECAT1_INT: R4.2; also elsewhere on the board
/ECAT_Extension/ESC_PHY_MDIO_DATA: R2.2; also elsewhere on the board
/ECAT_Extension/~ESC_PHY_RESETn~: R1.2; also elsewhere on the board
/ECAT_Extension/~SPI_CS1n~: JP3.2 (C); also elsewhere on the board
/ECAT_Extension/~SPI_CS2n~: JP7.2 (C); also elsewhere on the board
/Sensor Channel #1/RS485_~CS_n~: JP3.4 (A); also elsewhere on the board
/Sensor Channel #1/SPI_~CS_n~: JP3.1 (A); also elsewhere on the board
/Sensor Channel #1/SSI_~CS_n~: JP3.3 (B); also elsewhere on the board
/Sensor Channel #2/RS485_~CS_n~: JP7.4 (A); also elsewhere on the board
/Sensor Channel #2/SPI_~CS_n~: JP7.3 (B); also elsewhere on the board
/Sensor Channel #2/SSI_~CS_n~: JP7.1 (A); also elsewhere on the board
GND: C1.2, C2.2, D1.2, J1.1, U1.2; also elsewhere on the board
unnamed: J1.3, JP1.2 (C)
unnamed: R7.1, U1.1, U1.4 (-)
VDD_3V3: JP1.1 (A), R1.1, R2.1, R3.1, R4.1; also elsewhere on the board

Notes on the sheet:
ECAT0 : Strap2=0->PHY_ADDR0=0 ->2.2k resistor to GND ECAT1 : Strap2=1->PHY_ADDR0=1 ->2.2k resistor to VDD
